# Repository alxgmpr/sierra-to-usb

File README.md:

# Sierra / Quectel 2.5GbE PoE modem appliance

Multi-gigabit WAN design study for **EM9190, EM9293, RM520N-GL and
RM551E-GL**. No CM4/CM5. **RK3566 is the selected Linux packet-processor
candidate for evaluation**, with an independent STM32 recovery MCU. The exact
modem tuples and complete appliance remain unqualified. The complete engineering
capture is in [hardware/appliance.kicad_pro](hardware/appliance.kicad_pro).

**Feasibility gate remains open.** Manufacturer documentation establishes Sierra
PCIe endpoint/USB-device operation, not modem-hosted Ethernet. A switch does not
supply the missing host and drivers. Quectel offload is a candidate requiring
exact firmware and NIC qualification. No modem combination is qualified.

- [Requirements and confirmed decisions](REQUIREMENTS.md)
- [Architecture, manufacturer evidence, networking and recovery](docs/architecture.md)
- [Historical MCU-only packet-path comparison](docs/packet-path.svg)
- [RK3566 processor qualification and current block diagram](docs/rockchip-qualification.md)
- [Block diagram and BOM qualification status](docs/qualification-status.md)
- [Power and complete-cost estimates](docs/power-and-cost.md)
- [Reopened Rockchip Linux comparison and sourcing](docs/rockchip-options.md)
- [Actual KiCad recovery schematic](hardware/recovery.kicad_sch)
- [Implemented circuit, checks and outstanding qualification](hardware/README.md)

The full [30-sheet appliance schematic](hardware/appliance.kicad_sch) now captures
processor/RAM/eMMC, all supplies, 2.5GbE, isolated PoE, modem/SIM and recovery
interfaces: 663 components, 823 nets, **zero full ERC violations**.
[Review PDF](hardware/review/2026-10-07/appliance.pdf) and
[completion / release holds](docs/schematic-completion.md) are available.
All 663 PCB footprints are assigned, including 572 stock hand-solder variants.
Current CLI schematic/PCB parity is clean. October 7 native update-dialog
results are retained in the [footprint and model audit](docs/footprint-audit.md). Two BGA land-pattern/process
reviews, remaining model holds, current modem guides and physical/software
qualification remain open. Placement, routing and manufacturing release remain
pending.

The [October 21 BGA/model follow-up](docs/bga-model-review-2026-10-21.md)
adds six package-envelope models for 16 components (54 attached STEP assets total).
Eighteen missing-model holds and both BGA assembly-process holds remain explicit.

Previous designs remain only in Git history; none were restored for this work.

## Full schematic work — 2026-10-07

Complete appliance capture is saved in the canonical `hardware/appliance` project,
including the independent always-on supply and full recovery hierarchy. See
[completion evidence and release holds](docs/schematic-completion.md).

## Footprint and modem review — 2026-10-21

[Six-footprint review](docs/footprint-review-2026-10-21.md) closes four drawing
geometry holds and fixes TPS56837 paste/mask geometry and BGA grid rounding.
The two BGA PCB land/process holds remain. [Modem documentation gates](docs/modem-documentation.md)
record current download blockers and a PCIe-only RM520N order-code exclusion.
All four modem profiles remain unreleased. Full ERC and native parity still pass.

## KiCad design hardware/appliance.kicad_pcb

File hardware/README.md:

# Appliance schematic

The complete engineering capture is [appliance.kicad_sch](appliance.kicad_sch), with
30 sheets, 663 components and 823 native nets. Open [appliance.kicad_pro](appliance.kicad_pro)
in KiCad. [appliance.kicad_pcb](appliance.kicad_pcb) contains all 663 footprints
with native schematic links; placement and routing are still pending.

The remaining processor, boot storage, CPU power, Ethernet, isolated PoE,
modem power, M.2, SIM and USB isolation circuits are now captured. The engineering
capture passes full ERC at all severities, with **zero violations and no exclusions**.
Current CLI schematic/PCB parity is clean. The October 7 bidirectional native
update-dialog checks reported zero errors/warnings and no proposed changes. This is not a manufacturing or four-modem release.

[Review PDF](review/2026-10-07/appliance.pdf) ·
[Native BOM inventory](review/2026-10-07/bom.csv) ·
[Validation report](review/2026-10-07/capture-report.json) ·
[Footprint and model audit](../docs/footprint-audit.md) ·
[Detailed completion and release holds](../docs/schematic-completion.md)

## Reproduce and inspect

Requires KiCad CLI 10.99 (the version used for native Altium reference import) and
Python 3. Run without `python -O`; the checker uses assertions.

```sh
python3 hardware/check.py --output /tmp/sierra-appliance-check
python3 hardware/tools/check_board_sync.py --output /tmp/sierra-board-check
python3 hardware/tools/review_modem_power.py --output /tmp/modem-power-analysis.json
python3 hardware/tools/export_appliance.py --output /tmp/sierra-appliance-review
```

The checker validates the native netlist and all-severity ERC; all 565 RK3566,
200 RAM, 153 eMMC and other major-device contacts are accounted for. It checks
65 manufacturer DDR pair mappings, the complete retained TI bridge/flyback net
partitions, critical rail/reset/interface connections, four assembly-profile power
maps, deterministic identities and exact pad-number parity for all 663 assigned
footprints. Pad parity establishes identity, not a fabrication land-pattern review.
626 components use default KiCad footprints, including 572 stock hand-solder
variants. Existing package sizes are retained. All attached model paths resolve;
missing or mechanically unverified models are explicitly recorded in
[footprint-policy.json](footprint-policy.json). Imported TI embedded STEP assets
are now stored in the project.

The [BGA/model follow-up](../docs/bga-model-review-2026-10-21.md) records six new
package-envelope models covering 16 components, all 18 remaining missing-model
holds, and measured mask/stencil limits for the two unreleased BGAs. The full
checker validates model source hashes, attachment rotations and these holds;
`tools/check_model_reviews.py --geometry` additionally checks the six STEP solids
and sourced bounds with CadQuery.

Use the native Update PCB / Update Schematic dialogs for normal edits, with
reference relinking off. `build_capture.py` regenerates the original capture and
applies the footprint policy; it overwrites manual schematic graphics. Preserve
editor changes before regeneration. `sync_board.py` is only an unrouted-board
refresh helper and refuses routed boards.

The PDF was rendered and all 30 sheets inspected. Cropped modem content, a duplicate
crystal-ground wire and the recovery USB shell-pad model were corrected during review.

## Assembly and software obligations

The default is the Quectel stuffing pattern. R2011/R2012/R2013/R2016/R2017 and
C2036/C2037/C2038 are DNP. Sierra USB profiles require all eight populated after
exact module review. Never energize Quectel contacts 24, 38 or 68. The native
[profile file](reference/modem-assembly-profiles.json) is machine-checked; all four
profiles have `released: false`. This is assembly selection, not hot interchange.

The independent STM32 must keep main, modem and NIC loads off until an isolated
Class 6 grant is stable (TPH_N/TPL_N/BT_N = 0/1/0), and cut loads on loss of grant.
It controls power, reset and recovery while Linux runs the packet path. Firmware
for those policies and real recovery/traffic behavior still need qualification.
The no-detect SIM socket permits card changes only with modem power off.

Modem USB isolation is powered from the always-on rail. Hardware enables data
only with valid host power and modem power delayed by 180–420 ms. A latched eFuse,
independent monitor and explicit discharge support recovery; measured rail fall,
USB isolation, off-time and per-model timing remain required.

## Release holds

- Two BGA PCB land/mask/paste process holds remain: U801 RK3566 and U901 Micron RAM.
  The [October 21 review](../docs/footprint-review-2026-10-21.md) closes the other four
  drawing geometry holds and records the corrected native geometry.
  Exact land patterns, copper/mask/paste, orientation and retention need review.
  RK/RAM retain the audited ball centers; connector lands follow archived vendor
  drawings. The detailed audit records mask, stencil and mechanical limitations.
- The staged board has no routing or outline. All-severity physical DRC remains
  open; the native synchronization check reports the actual counts without
  suppressing rules. Do not export it for fabrication.
- [Current modem access and order-code gates](../docs/modem-documentation.md) remain open.
  RM520N Series V1.4 is login-gated; the archived V1.0 remains provisional.
  Current controlled EM919x and EM92xx technical specifications and the RM551E-GL
  production hardware guide remain unavailable. Older manufacturer guides and the
  RM520N V1.0 guide support provisional capture. Current pin/timing differences,
  exact firmware/composition and power envelopes must be closed per module.
- 5 A modem current is a provisional burst allocation. Connector hot derating,
  voltage drop, regulator stability/current, PoE startup/MPS/allocation, thermal,
  isolation/creepage, SI/EMC and RF operation require physical testing. HV MLCCs
  across isolation are not a certified safety-barrier assembly.
- CPU DVS/kernel/DDR training/eMMC/NIC drivers and unique Ethernet MAC provisioning
  require an actual software image and boot/traffic/recovery tests.

Sources, revisions and hashes are saved in [reference/sources.json](reference/sources.json).
TI's source archive retains its notices; imported symbols and footprints are derived
from TIDA-050023. The topology comparison excludes deleted evaluation headers,
auxiliary input and the old 1 GbE transformer. The new capture requests Class 6,
extracts all four PoE pairs with 2.5 GbE magnetics, and isolates allocation status.

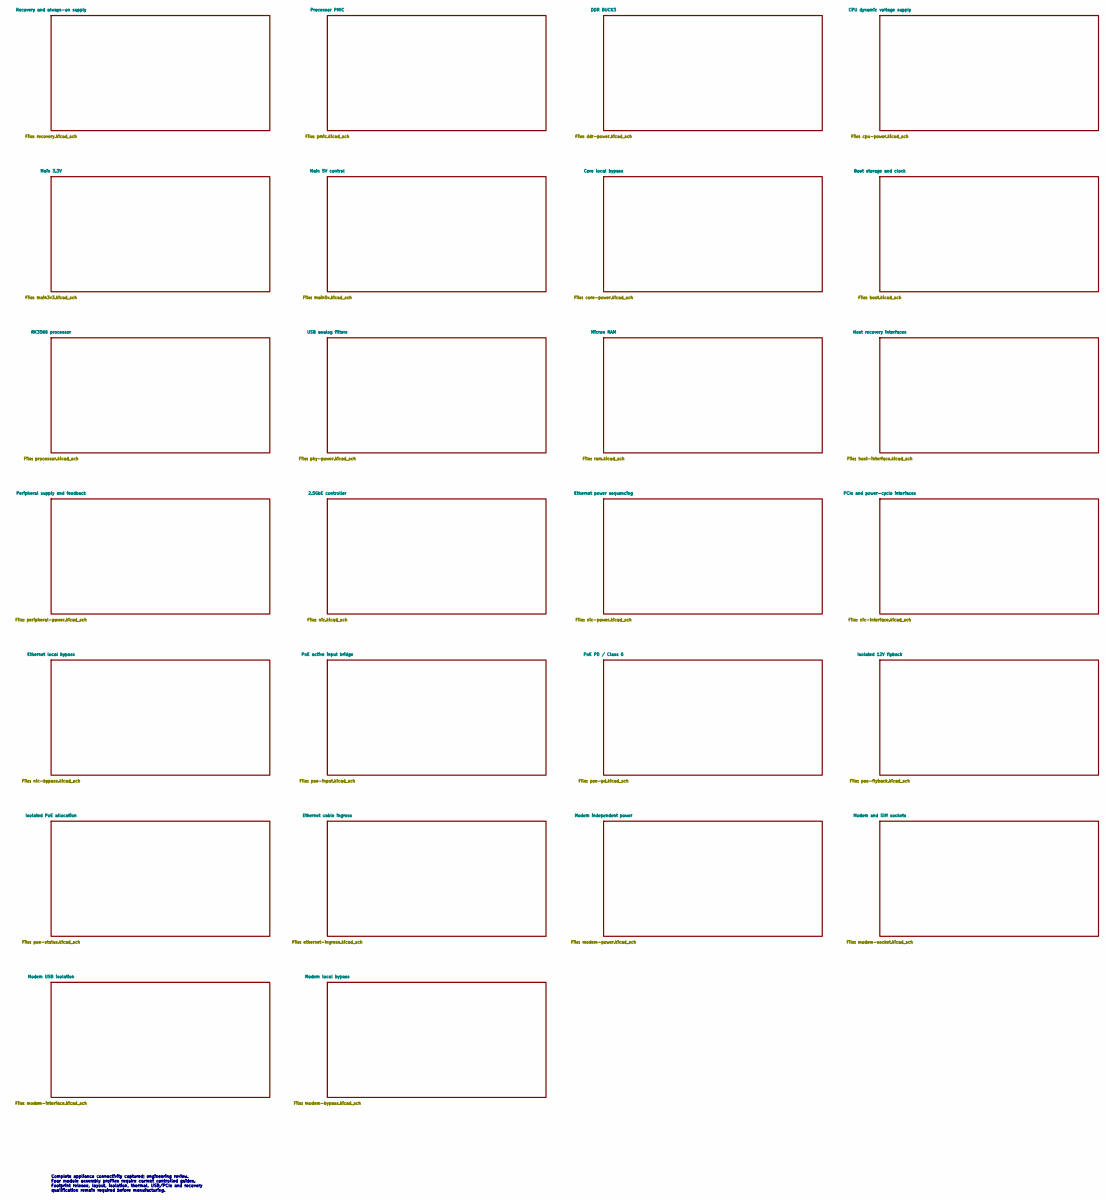
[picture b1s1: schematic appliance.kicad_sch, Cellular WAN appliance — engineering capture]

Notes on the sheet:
Complete appliance connectivity captured; engineering review. Four module assembly profiles require current controlled guides. Footprint release, layout, isolation, thermal, USB/PCIe and recovery qualification remain required before manufacturing.

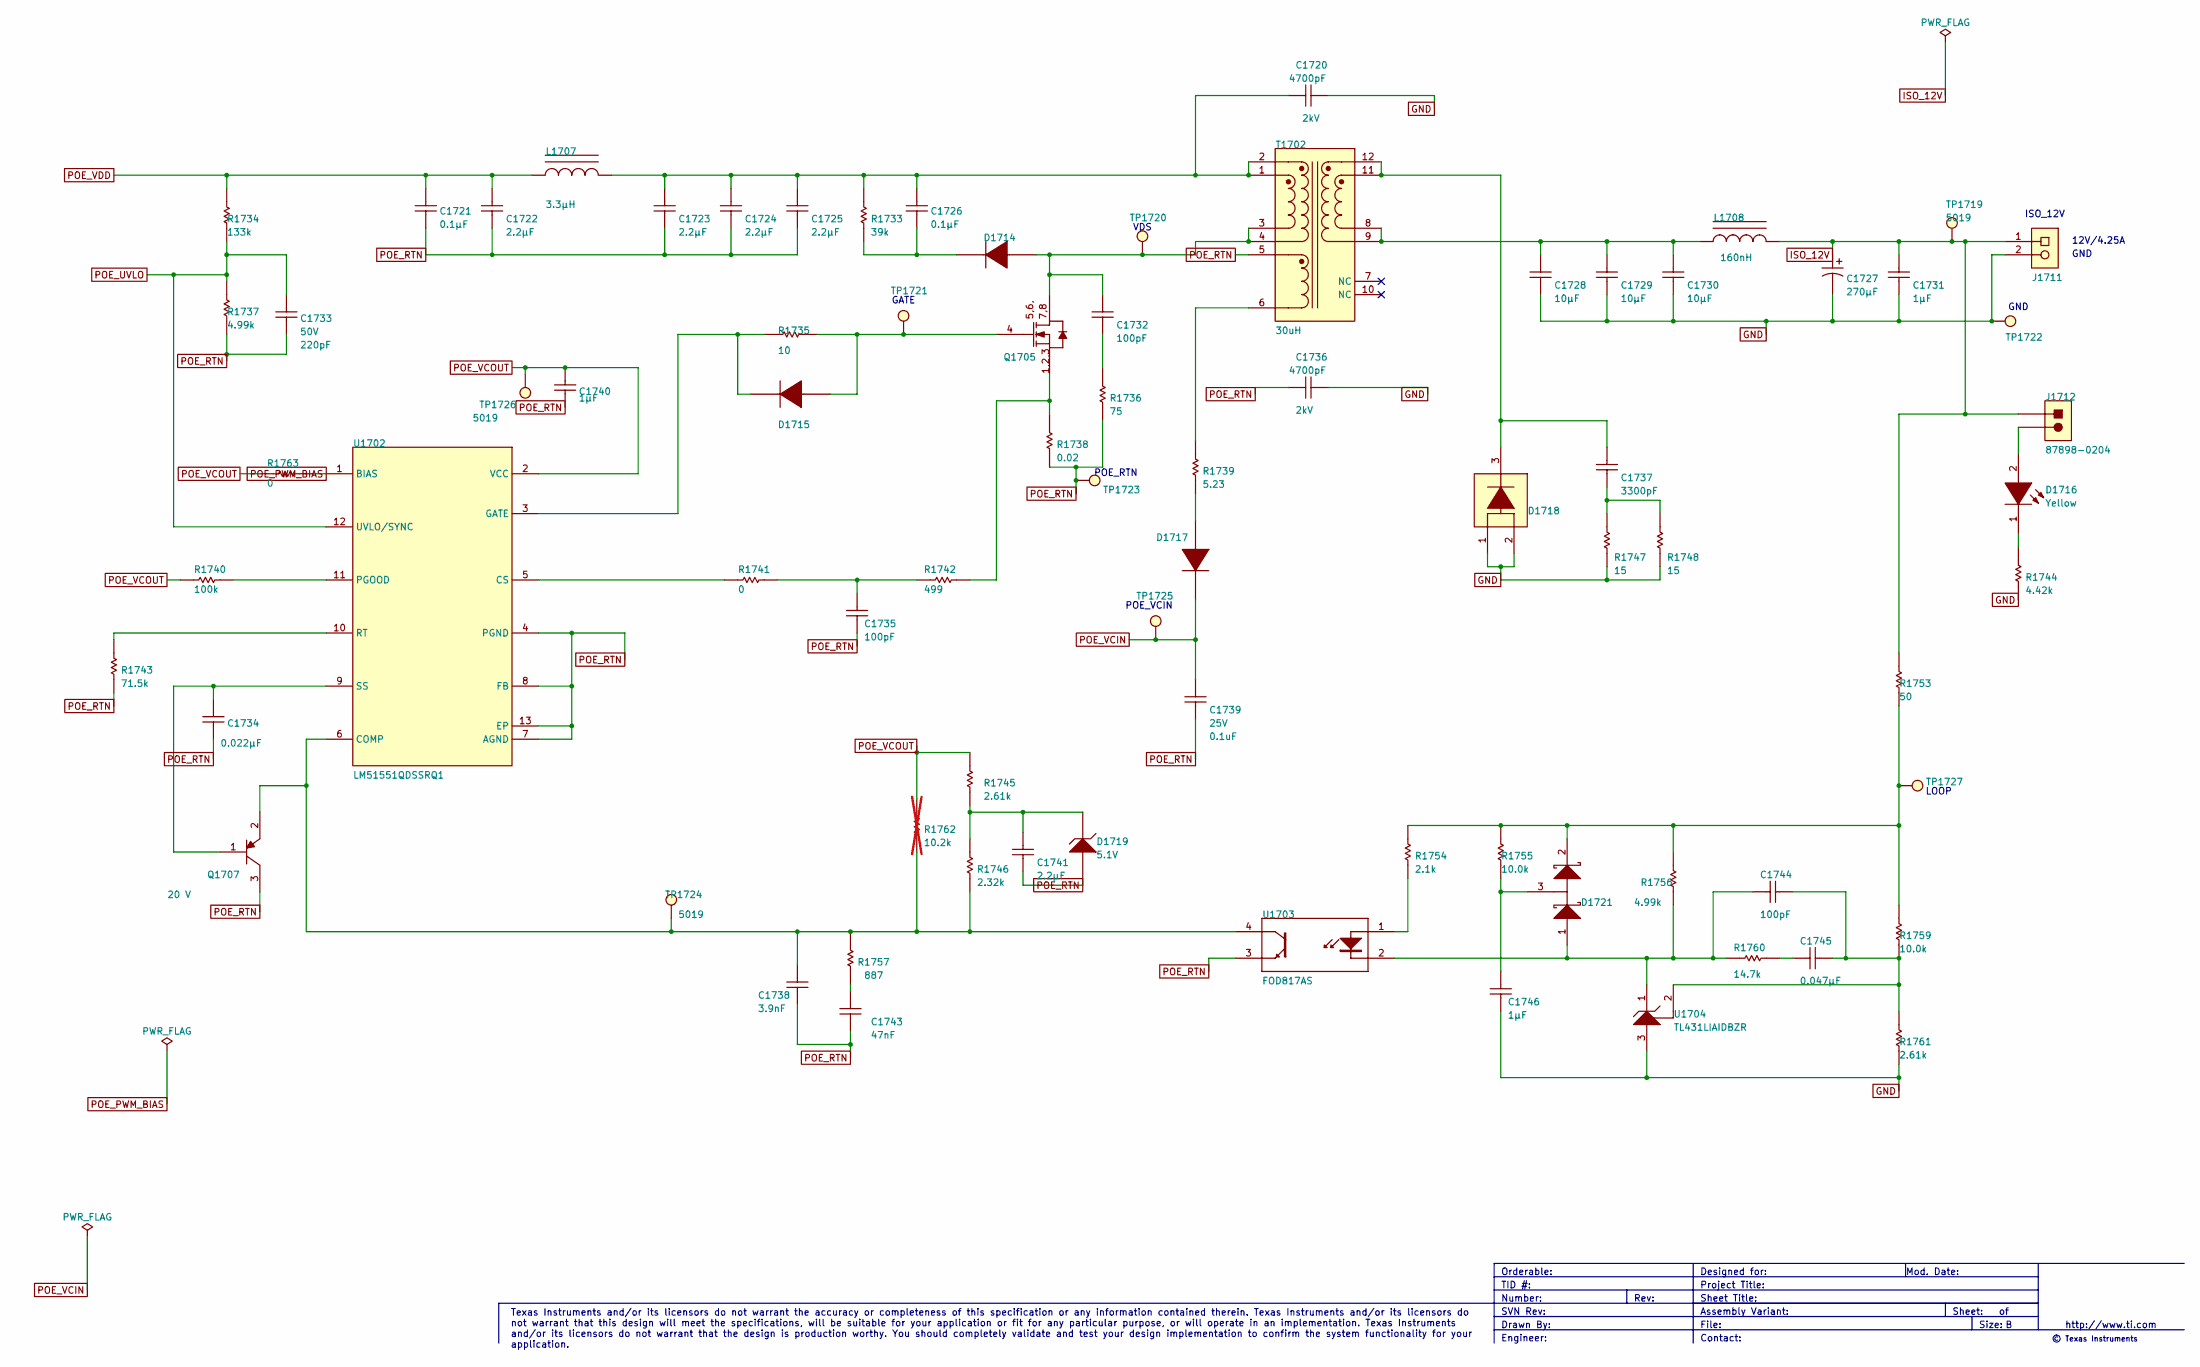
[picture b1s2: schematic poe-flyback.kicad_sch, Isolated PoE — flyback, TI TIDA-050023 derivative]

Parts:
C1720, C1736: 4700pF; C_1812_4532Metric_Pad1.57x3.40mm_HandSolder; TOLERANCE_% 10%; PARTNUMBER 1812GC472KAT1A
C1721, C1726: 0.1uF; C_0805_2012Metric_Pad1.18x1.45mm_HandSolder; TOLERANCE_% 10; PARTNUMBER C2012X7R2A104K125AA
C1722, C1723, C1724, C1725: 2.2uF; C_1210_3225Metric_Pad1.33x2.70mm_HandSolder; TOLERANCE_% 10; PARTNUMBER GRM32ER72A225KA35L
C1727: 270uF; TI_PCV_1000x1270; TOLERANCE_% 20; PARTNUMBER PCV1E271MCL1GS
C1728, C1729, C1730: 10uF; C_1210_3225Metric_Pad1.33x2.70mm_HandSolder; TOLERANCE_% 10; PARTNUMBER C1210C106K3RACTU
C1731, C1740, C1746: 1uF; C_0805_2012Metric_Pad1.18x1.45mm_HandSolder; TOLERANCE_% 10; PARTNUMBER GRM21BR71E105KA99L
C1732: 100pF; C_0805_2012Metric_Pad1.18x1.45mm_HandSolder; TOLERANCE_% 5; PARTNUMBER GRM21A5C2E101JW01D
C1733: 220pF; C_0603_1608Metric_Pad1.08x0.95mm_HandSolder; TOLERANCE_% 5%; PARTNUMBER C0603C221J5GACTU
C1734: 0.022uF; C_0603_1608Metric_Pad1.08x0.95mm_HandSolder; TOLERANCE_% 10; PARTNUMBER C0603C223K3RACTU
C1735, C1744: 100pF; C_0603_1608Metric_Pad1.08x0.95mm_HandSolder; TOLERANCE_% 5; PARTNUMBER GRM1885C1H101JA01D
C1737: 3300pF; C_0603_1608Metric_Pad1.08x0.95mm_HandSolder; TOLERANCE_% 10; PARTNUMBER GRM188R72A332KA01D
C1738: 3900pF; C_0603_1608Metric_Pad1.08x0.95mm_HandSolder; TOLERANCE_% 5%; PARTNUMBER GRM1885C1H392JA01D
C1739: 0.1uF; C_0603_1608Metric_Pad1.08x0.95mm_HandSolder; TOLERANCE_% 5%; PARTNUMBER 06033C104JAT2A
C1741: 2.2uF; C_0603_1608Metric_Pad1.08x0.95mm_HandSolder; TOLERANCE_% 10%; PARTNUMBER EMK107BB7225KA-T
C1743: 0.047uF; C_0603_1608Metric_Pad1.08x0.95mm_HandSolder; TOLERANCE_% 5%; PARTNUMBER 06033C473JAT2A
C1745: 0.047uF; C_0603_1608Metric_Pad1.08x0.95mm_HandSolder; TOLERANCE_% 10; PARTNUMBER C1608X7R1H473K080AA
D1714: 200V; D_SMA_Handsoldering; PARTNUMBER ES2DA-13-F
D1715, D1717: 100V; D_SOD-123; PARTNUMBER MMSD4148T1G
D1716: Yellow; LED_0603_1608Metric_Pad1.05x0.95mm_HandSolder; PARTNUMBER 150060YS75000
D1718: 60V; Diodes_PowerDI-5_3Pin_Derived; PARTNUMBER SBRT20U60SP5-7
D1719: 5.1V; D_SOD-123; PARTNUMBER MMSZ5231B-7-F
D1721: 30V; SOT-23_Handsoldering; PARTNUMBER BAT54S-7-F
J1711: ED555/2DS; TI_TERM_BLK_ED555-2DS; VOLTAGE_V 150; PARTNUMBER ED555/2DS
J1712: 87898-0204; TI_Molex_87898-0204; PARTNUMBER 87898-0204
L1707: 3.3uH; L_Coilcraft_XxL4020; PARTNUMBER XFL4020-332MEB
L1708: 160nH; L_Coilcraft_XAL5030-XXX; PARTNUMBER XAL5030-161MEB
Q1705: 150V; TI_TRANS_Fairchild_PQFN08A; PARTNUMBER FDMS86252
Q1707: 20 V; SOT-23_Handsoldering; PARTNUMBER FMMT718TA
R1733: 39k; R_1206_3216Metric_Pad1.30x1.75mm_HandSolder; TOLERANCE_% 5; PARTNUMBER CRCW120639K0JNEA
R1734: 133k; R_0603_1608Metric_Pad0.98x0.95mm_HandSolder; TOLERANCE_% 0.5%; PARTNUMBER RT0603DRE07133KL
R1735: 10; R_0603_1608Metric_Pad0.98x0.95mm_HandSolder; TOLERANCE_% 5%; PARTNUMBER CRCW060310R0JNEA
R1736: 75; R_2010_5025Metric_Pad1.40x2.65mm_HandSolder; TOLERANCE_% 5; PARTNUMBER CRCW201075R0JNEF
R1737: 4.99k; R_0603_1608Metric_Pad0.98x0.95mm_HandSolder; TOLERANCE_% 0.5; PARTNUMBER RT0603DRE074K99L
R1738: 0.02; R_2010_5025Metric_Pad1.40x2.65mm_HandSolder; TOLERANCE_% 1; PARTNUMBER CSRN2010FK20L0
R1739: 5.23; R_0805_2012Metric_Pad1.20x1.40mm_HandSolder; TOLERANCE_% 1; PARTNUMBER CRCW08055R23FKEA
R1740: 100k; R_0603_1608Metric_Pad0.98x0.95mm_HandSolder; TOLERANCE_% 1%; PARTNUMBER CRCW0603100KFKEA
R1741, R1763: 0; R_0603_1608Metric_Pad0.98x0.95mm_HandSolder; TOLERANCE_% 5; PARTNUMBER MCR03EZPJ000
R1742: 499; R_0603_1608Metric_Pad0.98x0.95mm_HandSolder; TOLERANCE_% 0.5%; PARTNUMBER RT0603DRE07499RL
R1743: 71.5k; R_0603_1608Metric_Pad0.98x0.95mm_HandSolder; TOLERANCE_% 0.5%; PARTNUMBER RT0603DRE0771K5L
R1744: 4.42k; R_0603_1608Metric_Pad0.98x0.95mm_HandSolder; TOLERANCE_% 1; PARTNUMBER CRCW06034K42FKEA
R1745: 2.61k; R_0603_1608Metric_Pad0.98x0.95mm_HandSolder; TOLERANCE_% 1%; PARTNUMBER CRCW06032K61FKEA
R1746: 2.32k; R_0603_1608Metric_Pad0.98x0.95mm_HandSolder; TOLERANCE_% 1%; PARTNUMBER CRCW06032K32FKEA
R1747, R1748: 15; R_2512_6332Metric_Pad1.40x3.35mm_HandSolder; TOLERANCE_% 5; PARTNUMBER CRCW251215R0JNEG
R1753: 50; R_0603_1608Metric_Pad0.98x0.95mm_HandSolder; TOLERANCE_% 1; PARTNUMBER CRCW060350R0FKEA
R1754: 2.10k; R_0603_1608Metric_Pad0.98x0.95mm_HandSolder; TOLERANCE_% 1%; PARTNUMBER CRCW06032K10FKEA
R1755, R1759: 10.0k; R_0603_1608Metric_Pad0.98x0.95mm_HandSolder; TOLERANCE_% 1; PARTNUMBER CRCW060310K0FKEA
R1756: 4.99k; R_0603_1608Metric_Pad0.98x0.95mm_HandSolder; TOLERANCE_% 1; PARTNUMBER CRCW06034K99FKEA
R1757: 887; R_0603_1608Metric_Pad0.98x0.95mm_HandSolder; TOLERANCE_% 1%; PARTNUMBER CRCW0603887RFKEA
R1760: 14.7k; R_0603_1608Metric_Pad0.98x0.95mm_HandSolder; TOLERANCE_% 1; PARTNUMBER CRCW060314K7FKEA
R1761: 2.61k; R_0603_1608Metric_Pad0.98x0.95mm_HandSolder; TOLERANCE_% 1; PARTNUMBER CRCW06032K61FKEA
R1762: 10.2k; R_0603_1608Metric_Pad0.98x0.95mm_HandSolder; TOLERANCE_% 1%; PARTNUMBER CRCW060310K2FKEA; not fitted
T1702: 30uH; TI_Wurth_EFD25_4476; PARTNUMBER 750317065
TP1719, TP1720, TP1721, TP1722, TP1723, TP1724, TP1725, TP1726, TP1727: 5019; TI_Keystone_5019; PARTNUMBER 5019
U1702: LM51551QDSSRQ1; WSON-12-1EP_3x2mm_P0.5mm_EP1x2.65; PARTNUMBER LM51551QDSSRQ1
U1703: FOD817AS; TI_N04C; VOLTAGE_ISOLATION_VRMS 5000V; PARTNUMBER FOD817AS
U1704: TL431LIAIDBZR; SOT-23_Handsoldering; PARTNUMBER TL431LIAIDBZR

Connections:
GND: C1720.1, C1727.2 (-), C1728.2, C1729.2, C1730.2, C1731.2, C1736.1, C1746.2, D1718.1 (A), D1718.2 (A), J1711.2, R1744.1, R1747.1, R1748.1, R1761.1, TP1722.1, U1704.3 (ANODE); also elsewhere on the board
ISO_12V: C1727.1 (+), C1731.1, J1711.1, J1712.1, L1708.2, R1753.2, TP1719.1; also elsewhere on the board
unnamed: C1720.2, C1723.1, C1724.1, C1725.1, C1726.2, L1707.2, R1733.2, T1702.1, T1702.2
unnamed: C1728.1, C1729.1, C1730.1, L1708.1, T1702.8, T1702.9
unnamed: C1732.2, R1736.2
unnamed: C1735.1, R1741.2, R1742.1
unnamed: C1737.2, R1747.2, R1748.2
unnamed: C1743.1, R1757.1
unnamed: C1745.2, R1760.2
unnamed: C1732.1, D1714.2 (A), Q1705.5 (D), Q1705.6 (D), Q1705.7 (D), Q1705.8 (D), T1702.3, T1702.4, TP1720.1
unnamed: C1726.1, D1714.1 (K), R1733.1
unnamed: D1715.2 (A), Q1705.4 (G), R1735.2, TP1721.1
unnamed: D1715.1 (K), R1735.1, U1702.3 (GATE)
unnamed: D1716.2 (A), J1712.2
unnamed: D1716.1 (K), R1744.2
unnamed: D1717.2 (A), R1739.1
unnamed: C1737.1, D1718.3 (K), T1702.11, T1702.12
unnamed: C1741.1, D1719.1 (K), R1745.1, R1746.2
unnamed: C1746.1, D1721.3 (C), R1755.1
unnamed: D1721.2 (K), R1753.1, R1754.2, R1755.2, R1756.2, R1759.2, TP1727.1
unnamed: Q1705.1 (S), Q1705.2 (S), Q1705.3 (S), R1738.2, R1742.2
unnamed: C1734.1, Q1707.1 (B), U1702.9 (SS)
unnamed: R1739.2, T1702.6
unnamed: R1741.1, U1702.5 (CS)
unnamed: R1740.2, U1702.11 (PGOOD)
unnamed: R1743.2, U1702.10 (RT)
unnamed: R1754.1, U1703.1 (A)
unnamed: C1744.1, C1745.1, R1759.1, R1761.2, U1704.2 (REF)
POE_PWM_BIAS: R1763.2, U1702.1 (BIAS)
POE_RTN: C1721.1, C1722.2, C1723.2, C1724.2, C1725.2, C1733.2, C1734.2, C1735.2, C1736.2, C1738.2, C1739.2, C1740.2, C1741.2, C1743.2, D1719.2 (A), Q1707.3 (C), R1736.1, R1737.1, R1738.1, R1743.1, T1702.5, TP1723.1, U1702.4 (PGND), U1702.7 (AGND), U1702.8 (FB), U1702.13 (EP), U1703.3 (E); also elsewhere on the board
POE_UVLO: C1733.1, R1734.1, R1737.2, U1702.12 (UVLO/SYNC); also elsewhere on the board
POE_VCIN: C1739.1, D1717.1 (K), TP1725.1; also elsewhere on the board
POE_VCOUT: C1740.1, R1740.1, R1745.2, R1762.2, R1763.1, TP1726.1, U1702.2 (VCC); also elsewhere on the board
POE_VDD: C1721.2, C1722.1, L1707.1, R1734.2; also elsewhere on the board

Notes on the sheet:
GND
TID #:
© Texas Instruments
Assembly Variant:
Sheet:
Number:
Orderable:
Designed for:
Mod. Date:
GATE
Sheet Title:
POE_RTN
Contact:
Rev:
VDS
File:
Drawn By:
12V/4.25A
Project Title:
SVN Rev:
Engineer:
POE_VCIN
LOOP
ISO_12V
Size:
http://www.ti.com
Texas Instruments and/or its licensors do not warrant the accuracy or completeness of this specification or any information contained therein. Texas Instruments and/or its licensors do not warrant that this design will meet the specifications, will be suitable for your application or fit for any pa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

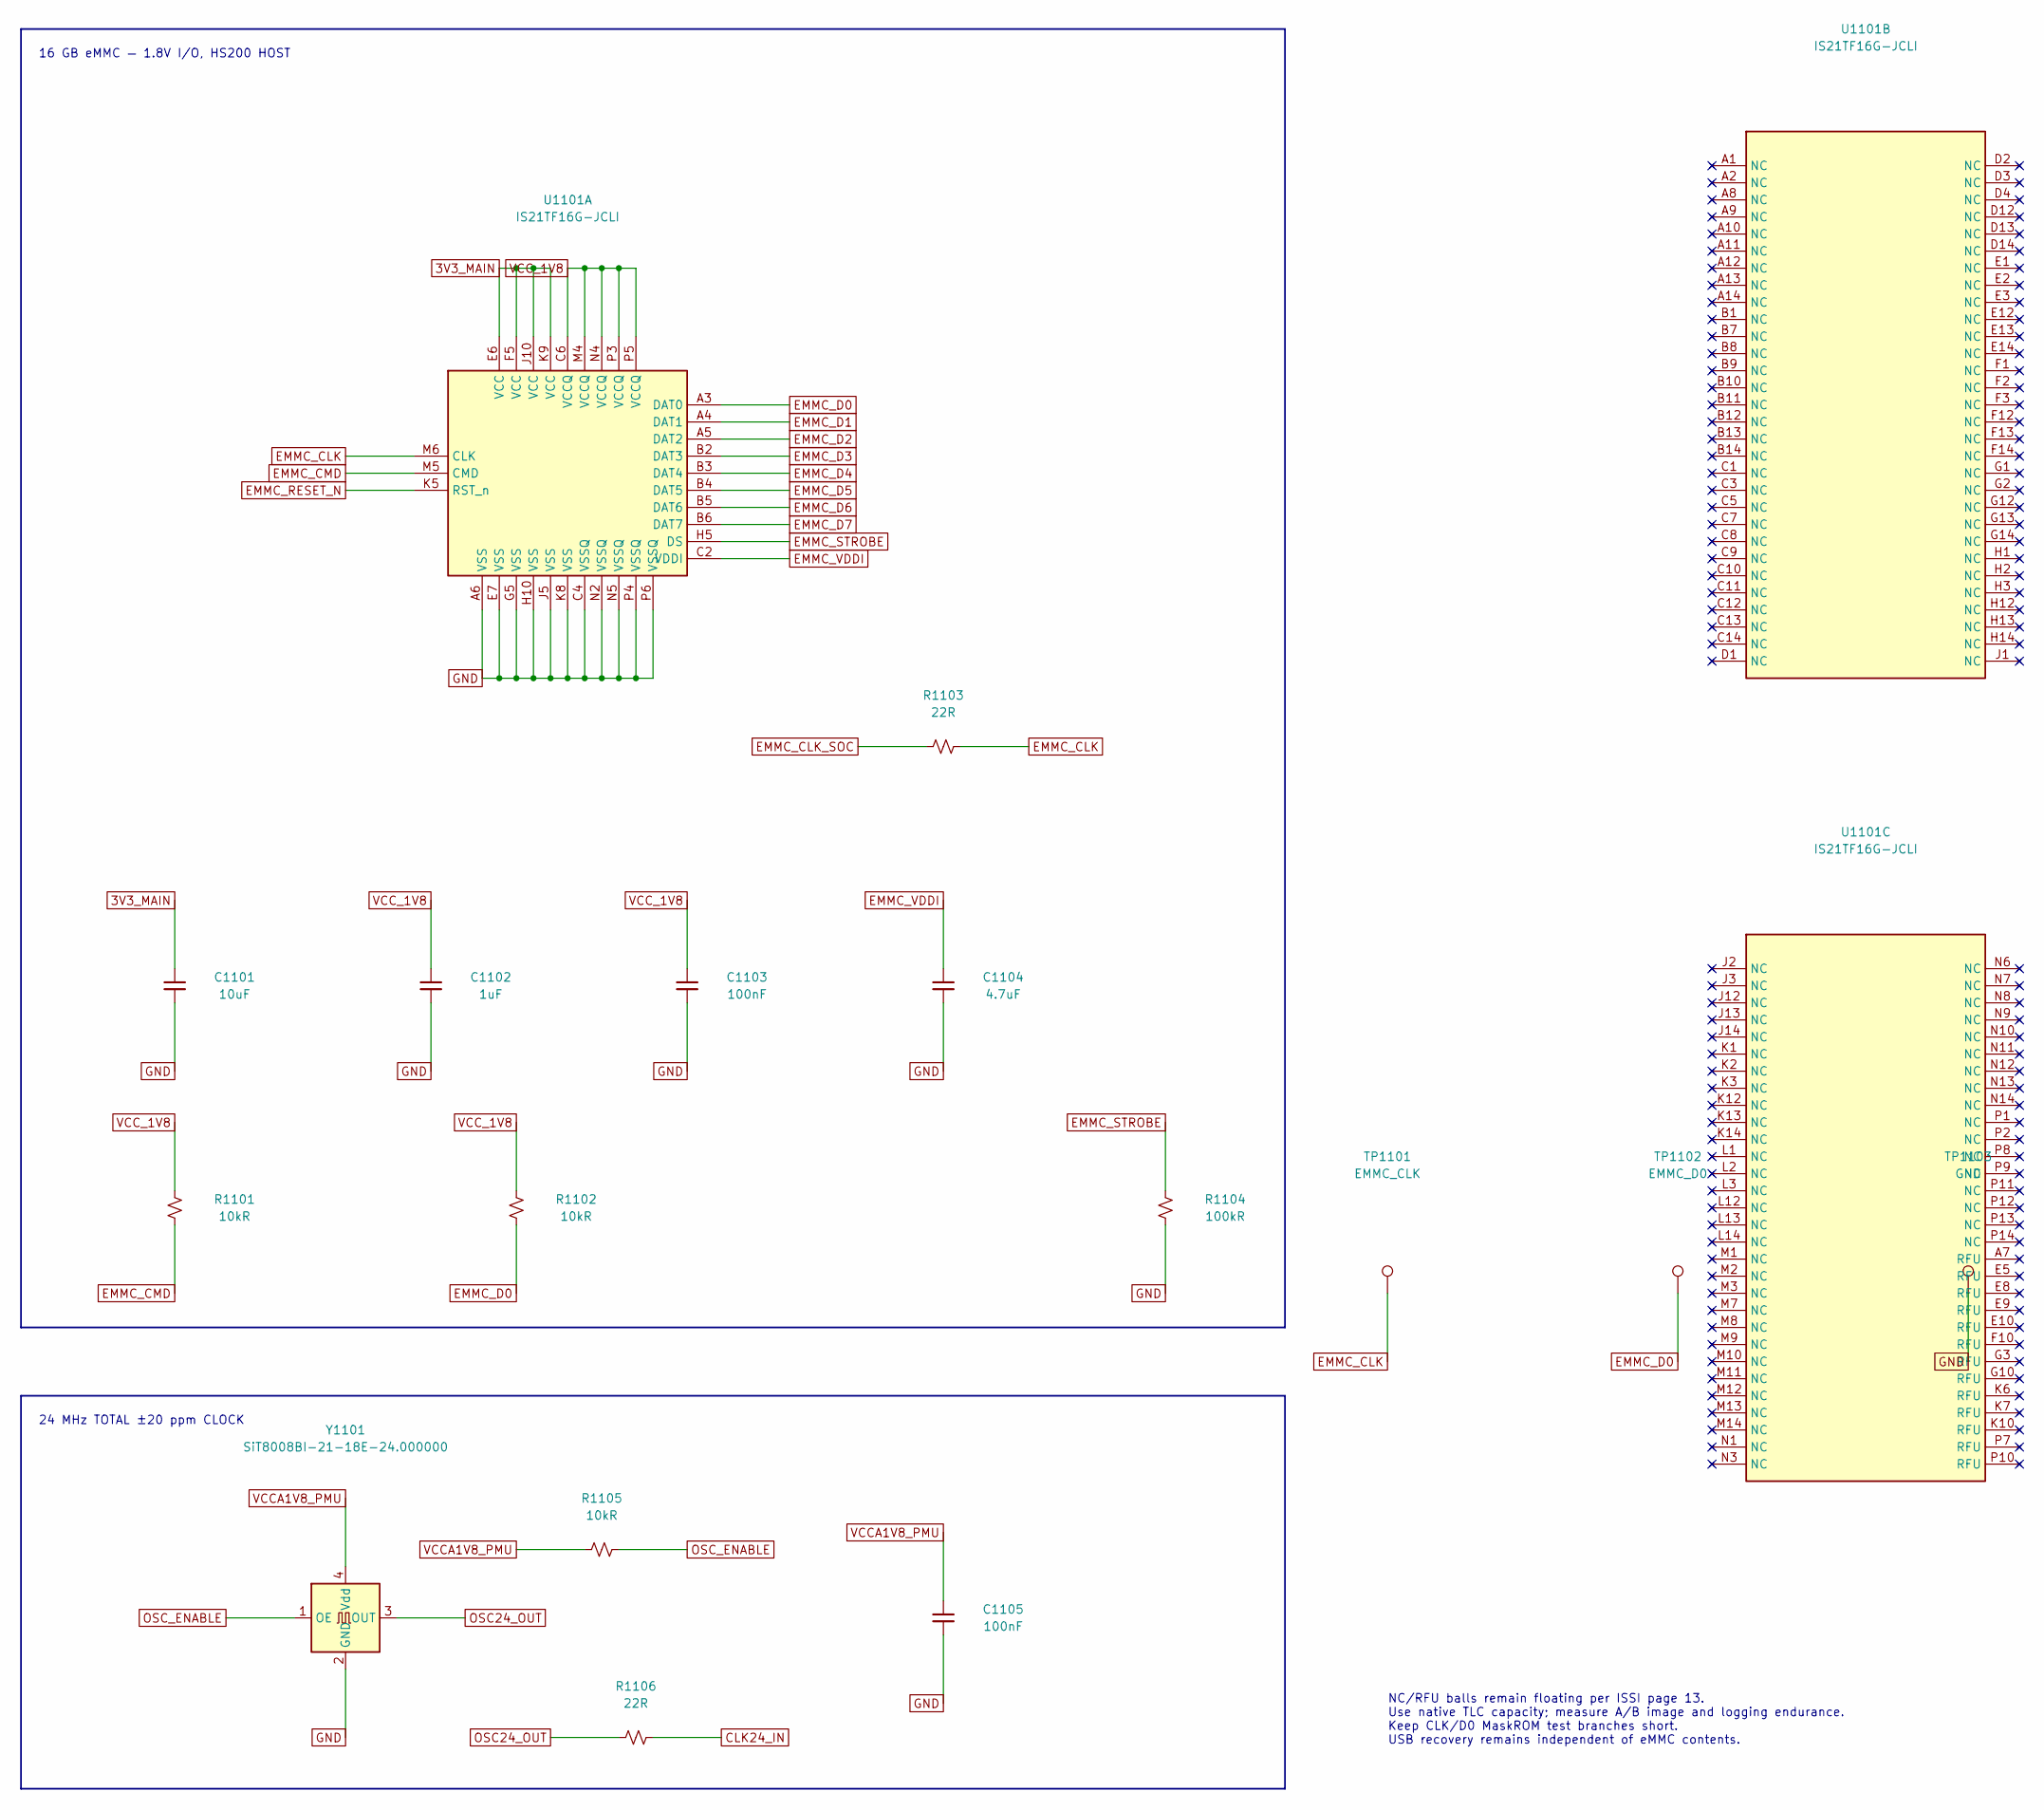
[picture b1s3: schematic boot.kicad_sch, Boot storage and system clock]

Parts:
C1101: 10uF; C_1206_3216Metric_Pad1.33x1.80mm_HandSolder; Voltage Rating 25V; MPN CL31B106KAHNNNE
C1102: 1uF; C_0603_1608Metric_Pad1.08x0.95mm_HandSolder; Voltage Rating 25V; MPN CL10B105KA8NNNC
C1103, C1105: 100nF; C_0603_1608Metric_Pad1.08x0.95mm_HandSolder; Voltage Rating 25V; MPN CL10B104KA8NNNC
C1104: 4.7uF; C_0603_1608Metric_Pad1.08x0.95mm_HandSolder; Voltage Rating 25V; MPN CL10A475KA8NQNC
R1101, R1102, R1105: 10kR; R_0603_1608Metric_Pad0.98x0.95mm_HandSolder; Tolerance 1%; Power Rating 0.1W; MPN RC0603FR-0710KL
R1103, R1106: 22R; R_0603_1608Metric_Pad0.98x0.95mm_HandSolder; Tolerance 1%; Power Rating 0.1W; MPN RC0603FR-0722RL
R1104: 100kR; R_0603_1608Metric_Pad0.98x0.95mm_HandSolder; Tolerance 1%; Power Rating 0.1W; MPN RC0603FR-07100KL
TP1101: EMMC_CLK; TestPoint_Pad_D1.0mm
TP1102: EMMC_D0; TestPoint_Pad_D1.0mm
TP1103: GND; TestPoint_Pad_D1.0mm
U1101: IS21TF16G-JCLI; LFBGA-153_11.5x13mm_Layout14x14_P0.5mm; MPN IS21TF16G-JCLI; LCSC C17441928
Y1101: SiT8008BI-21-18E-24.000000; Oscillator_SMD_SiT_PQFN-4Pin_3.2x2.5mm; Supply Voltage 1.8V; MPN SiT8008BI-21-18E-24.000000; LCSC C820729

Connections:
3V3_MAIN: C1101.1, U1101.E6 (VCC), U1101.F5 (VCC), U1101.J10 (VCC), U1101.K9 (VCC); also elsewhere on the board
CLK24_IN: R1106.2; also elsewhere on the board
EMMC_CLK: R1103.2, TP1101.1 (1_1), U1101.M6 (CLK)
EMMC_CLK_SOC: R1103.1; also elsewhere on the board
EMMC_CMD: R1101.2, U1101.M5 (CMD); also elsewhere on the board
EMMC_D0: R1102.2, TP1102.1 (1_1), U1101.A3 (DAT0); also elsewhere on the board
EMMC_D1: U1101.A4 (DAT1); also elsewhere on the board
EMMC_D2: U1101.A5 (DAT2); also elsewhere on the board
EMMC_D3: U1101.B2 (DAT3); also elsewhere on the board
EMMC_D4: U1101.B3 (DAT4); also elsewhere on the board
EMMC_D5: U1101.B4 (DAT5); also elsewhere on the board
EMMC_D6: U1101.B5 (DAT6); also elsewhere on the board
EMMC_D7: U1101.B6 (DAT7); also elsewhere on the board
EMMC_RESET_N: U1101.K5 (RST_n); also elsewhere on the board
EMMC_STROBE: R1104.1, U1101.H5 (DS); also elsewhere on the board
EMMC_VDDI: C1104.1, U1101.C2 (VDDI)
GND: C1101.2, C1102.2, C1103.2, C1104.2, C1105.2, R1104.2, TP1103.1 (1_1), U1101.A6 (VSS), U1101.C4 (VSSQ), U1101.E7 (VSS), U1101.G5 (VSS), U1101.H10 (VSS), U1101.J5 (VSS), U1101.K8 (VSS), U1101.N2 (VSSQ), U1101.N5 (VSSQ), U1101.P4 (VSSQ), U1101.P6 (VSSQ), Y1101.2 (GND); also elsewhere on the board
OSC24_OUT: R1106.1, Y1101.3 (OUT)
OSC_ENABLE: R1105.2, Y1101.1 (OE)
VCCA1V8_PMU: C1105.1, R1105.1, Y1101.4 (Vdd); also elsewhere on the board
VCC_1V8: C1102.1, C1103.1, R1101.1, R1102.1, U1101.C6 (VCCQ), U1101.M4 (VCCQ), U1101.N4 (VCCQ), U1101.P3 (VCCQ), U1101.P5 (VCCQ); also elsewhere on the board

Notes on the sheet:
16 GB eMMC — 1.8V I/O, HS200 HOST
NC/RFU balls remain floating per ISSI page 13. Use native TLC capacity; measure A/B image and logging endurance. Keep CLK/D0 MaskROM test branches short. USB recovery remains independent of eMMC contents.
24 MHz TOTAL ±20 ppm CLOCK
